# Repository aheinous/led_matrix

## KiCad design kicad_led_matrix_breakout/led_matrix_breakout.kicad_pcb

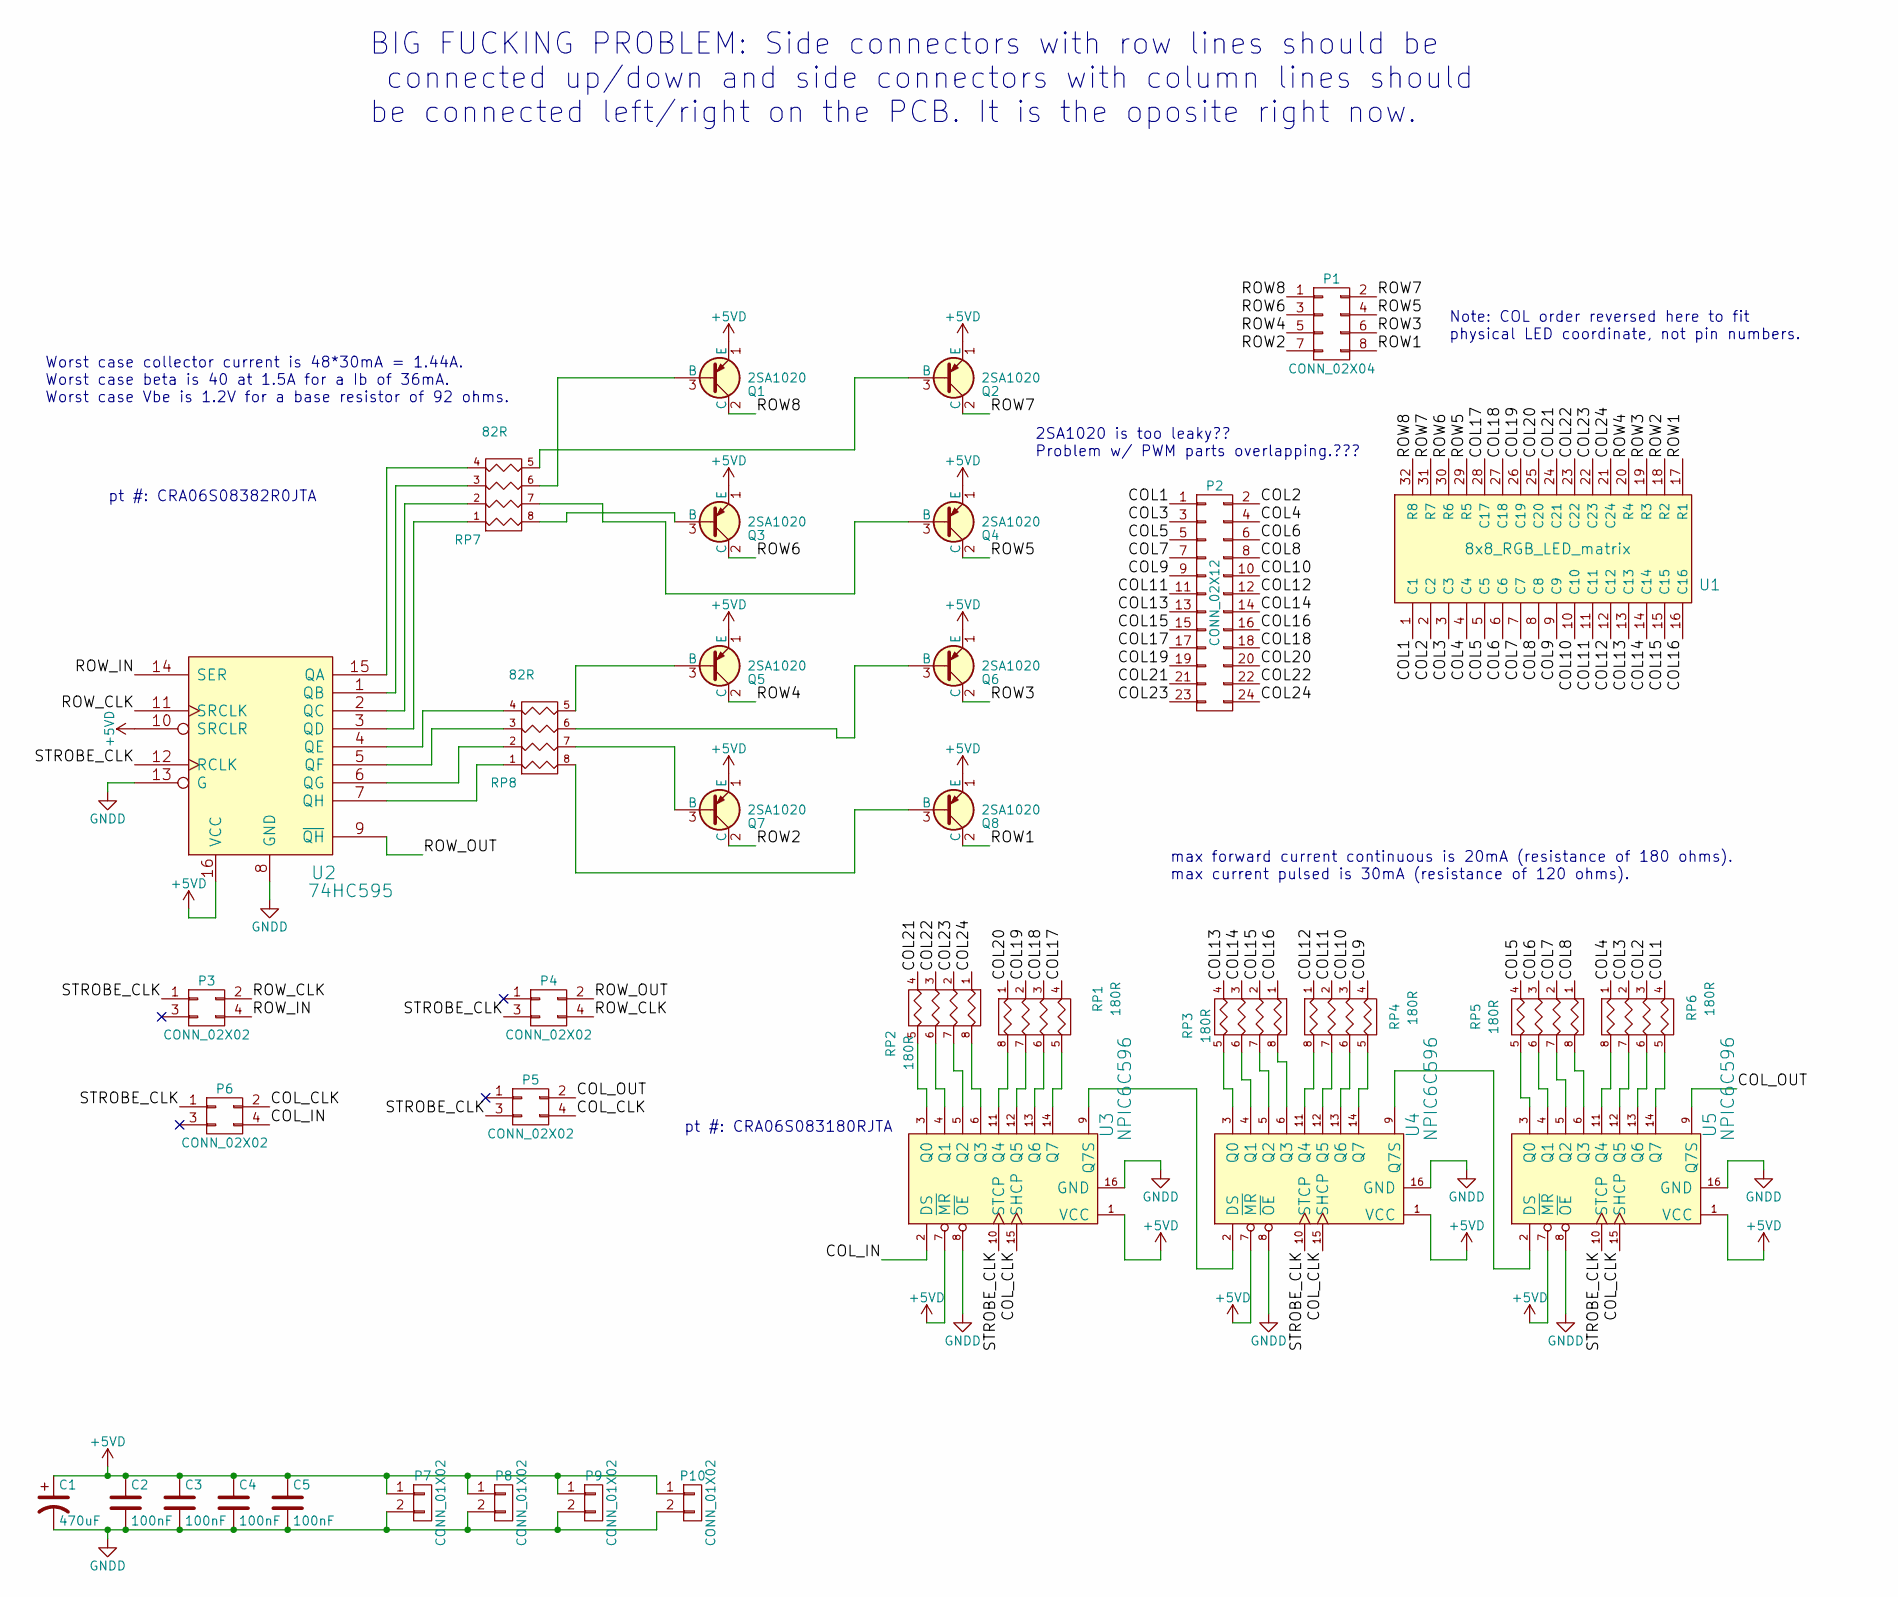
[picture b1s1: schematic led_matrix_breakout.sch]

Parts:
C1: 470uF; c_elec_10x10
C2, C3, C4, C5: 100nF; C_0805_HandSoldering
P1: CONN_02X04; Pin_Header_Straight_2x04
P2: CONN_02X12; Pin_Header_Straight_2x12
P3, P4, P5, P6: CONN_02X02; 2x2_edge_header_new
P7, P8, P9, P10: CONN_01X02; 2x1_edge_header_new
Q1, Q2, Q3, Q4, Q5, Q6, Q7, Q8: 2SA1020; TO-92_Inline_Narrow_Oval
RP1, RP2, RP3, RP4, RP5, RP6: 180R; CRA06S_4_resistor_array
RP7, RP8: 82R; CRA06S_4_resistor_array
U1: 8x8_RGB_LED_matrix; 8x8_RGB_led_matrix_60mmx60mm
U2: 74HC595; SSOP-16_4.4x5.2mm_Pitch0.65mm
U3, U4, U5: NPIC6C596; SSOP-16_4.4x5.2mm_Pitch0.65mm

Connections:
+5VD: C1.1, C2.1, C3.1, C4.1, C5.1, P7.1, P8.1, P9.1, P10.1, Q1.1 (E), Q2.1 (E), Q3.1 (E), Q4.1 (E), Q5.1 (E), Q6.1 (E), Q7.1 (E), Q8.1 (E), U2.10 (SRCLR), U2.16 (VCC), U3.1 (VCC), U3.7 (~MR), U4.1 (VCC), U4.7 (~MR), U5.1 (VCC), U5.7 (~MR)
/COL1: P2.1, RP6.4, U1.1 (C1); also elsewhere on the board
/COL2: P2.2, RP6.3, U1.2 (C2); also elsewhere on the board
/COL3: P2.3, RP6.2, U1.3 (C3); also elsewhere on the board
/COL4: P2.4, RP6.1, U1.4 (C4); also elsewhere on the board
/COL5: P2.5, RP5.4, U1.5 (C5); also elsewhere on the board
/COL6: P2.6, RP5.3, U1.6 (C6); also elsewhere on the board
/COL7: P2.7, RP5.2, U1.7 (C7); also elsewhere on the board
/COL8: P2.8, RP5.1, U1.8 (C8); also elsewhere on the board
/COL9: P2.9, RP4.4, U1.9 (C9); also elsewhere on the board
/COL10: P2.10, RP4.3, U1.10 (C10); also elsewhere on the board
/COL11: P2.11, RP4.2, U1.11 (C11); also elsewhere on the board
/COL12: P2.12, RP4.1, U1.12 (C12); also elsewhere on the board
/COL13: P2.13, RP3.4, U1.13 (C13); also elsewhere on the board
/COL14: P2.14, RP3.3, U1.14 (C14); also elsewhere on the board
/COL15: P2.15, RP3.2, U1.15 (C15); also elsewhere on the board
/COL16: P2.16, RP3.1, U1.16 (C16); also elsewhere on the board
/COL17: P2.17, RP1.4, U1.28 (C17); also elsewhere on the board
/COL18: P2.18, RP1.3, U1.27 (C18); also elsewhere on the board
/COL19: P2.19, RP1.2, U1.26 (C19); also elsewhere on the board
/COL20: P2.20, RP1.1, U1.25 (C20); also elsewhere on the board
/COL21: P2.21, RP2.4, U1.24 (C21); also elsewhere on the board
/COL22: P2.22, RP2.3, U1.23 (C22); also elsewhere on the board
/COL23: P2.23, RP2.2, U1.22 (C23); also elsewhere on the board
/COL24: P2.24, RP2.1, U1.21 (C24); also elsewhere on the board
/COL_CLK: P5.4, P6.2, U3.15 (SHCP), U4.15 (SHCP), U5.15 (SHCP)
/COL_IN: P6.4, U3.2 (DS)
/COL_OUT: P5.2, U5.9 (Q7S)
/ROW1: P1.8, Q8.2 (C), U1.17 (R1); also elsewhere on the board
/ROW2: P1.7, Q7.2 (C), U1.18 (R2); also elsewhere on the board
/ROW3: P1.6, Q6.2 (C), U1.19 (R3); also elsewhere on the board
/ROW4: P1.5, Q5.2 (C), U1.20 (R4); also elsewhere on the board
/ROW5: P1.4, Q4.2 (C), U1.29 (R5); also elsewhere on the board
/ROW6: P1.3, Q3.2 (C), U1.30 (R6); also elsewhere on the board
/ROW7: P1.2, Q2.2 (C), U1.31 (R7); also elsewhere on the board
/ROW8: P1.1, Q1.2 (C), U1.32 (R8); also elsewhere on the board
/ROW_CLK: P3.2, P4.4, U2.11 (SRCLK)
/ROW_IN: P3.4, U2.14 (SER)
/ROW_OUT: P4.2, U2.9 (~QH)
/STROBE_CLK: P3.1, P4.3, P5.3, P6.1, U2.12 (RCLK), U3.10 (STCP), U4.10 (STCP), U5.10 (STCP)
GNDD: C1.2, C2.2, C3.2, C4.2, C5.2, P7.2, P8.2, P9.2, P10.2, U2.8 (GND), U2.13 (G), U3.8 (~OE), U3.16 (GND), U4.8 (~OE), U4.16 (GND), U5.8 (~OE), U5.16 (GND)
unnamed: Q1.3 (B), RP7.6 (R3)
unnamed: Q2.3 (B), RP7.5 (R4)
unnamed: Q3.3 (B), RP7.8 (R1)
unnamed: Q4.3 (B), RP7.7 (R2)
unnamed: Q5.3 (B), RP8.5 (R4)
unnamed: Q6.3 (B), RP8.6 (R3)
unnamed: Q7.3 (B), RP8.7 (R2)
unnamed: Q8.3 (B), RP8.8 (R1)
unnamed: RP1.5 (R4), U3.14 (Q7)
unnamed: RP1.6 (R3), U3.13 (Q6)
unnamed: RP1.7 (R2), U3.12 (Q5)
unnamed: RP1.8 (R1), U3.11 (Q4)
unnamed: RP2.5 (R4), U3.3 (Q0)
unnamed: RP2.6 (R3), U3.4 (Q1)
unnamed: RP2.7 (R2), U3.5 (Q2)
unnamed: RP2.8 (R1), U3.6 (Q3)
unnamed: RP3.5 (R4), U4.3 (Q0)
unnamed: RP3.6 (R3), U4.4 (Q1)
unnamed: RP3.7 (R2), U4.5 (Q2)
unnamed: RP3.8 (R1), U4.6 (Q3)
unnamed: RP4.5 (R4), U4.14 (Q7)
unnamed: RP4.6 (R3), U4.13 (Q6)
unnamed: RP4.7 (R2), U4.12 (Q5)
unnamed: RP4.8 (R1), U4.11 (Q4)
unnamed: RP5.5 (R4), U5.3 (Q0)
unnamed: RP5.6 (R3), U5.4 (Q1)
unnamed: RP5.7 (R2), U5.5 (Q2)
unnamed: RP5.8 (R1), U5.6 (Q3)
unnamed: RP6.5 (R4), U5.14 (Q7)
unnamed: RP6.6 (R3), U5.13 (Q6)
unnamed: RP6.7 (R2), U5.12 (Q5)
unnamed: RP6.8 (R1), U5.11 (Q4)
unnamed: RP7.1, U2.3 (QD)
unnamed: RP7.2, U2.2 (QC)
unnamed: RP7.3, U2.1 (QB)
unnamed: RP7.4, U2.15 (QA)
unnamed: RP8.1, U2.7 (QH)
unnamed: RP8.2, U2.6 (QG)
unnamed: RP8.3, U2.5 (QF)
unnamed: RP8.4, U2.4 (QE)
unnamed: U3.9 (Q7S), U4.2 (DS)
unnamed: U4.9 (Q7S), U5.2 (DS)

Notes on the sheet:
max forward current continuous is 20mA (resistance of 180 ohms). max current pulsed is 30mA (resistance of 120 ohms).
Worst case collector current is 48*30mA = 1.44A. Worst case beta is 40 at 1.5A for a Ib of 36mA. Worst case Vbe is 1.2V for a base resistor of 92 ohms.
pt #: CRA06S08382R0JTA
pt #: CRA06S083180RJTA
Note: COL order reversed here to fit physical LED coordinate, not pin numbers.
BIG FUCKING PROBLEM: Side connectors with row lines should be connected up/down and side connectors with column lines should be connected left/right on the PCB. It is the oposite right now.
2SA1020 is too leaky?? Problem w/ PWM parts overlapping.???

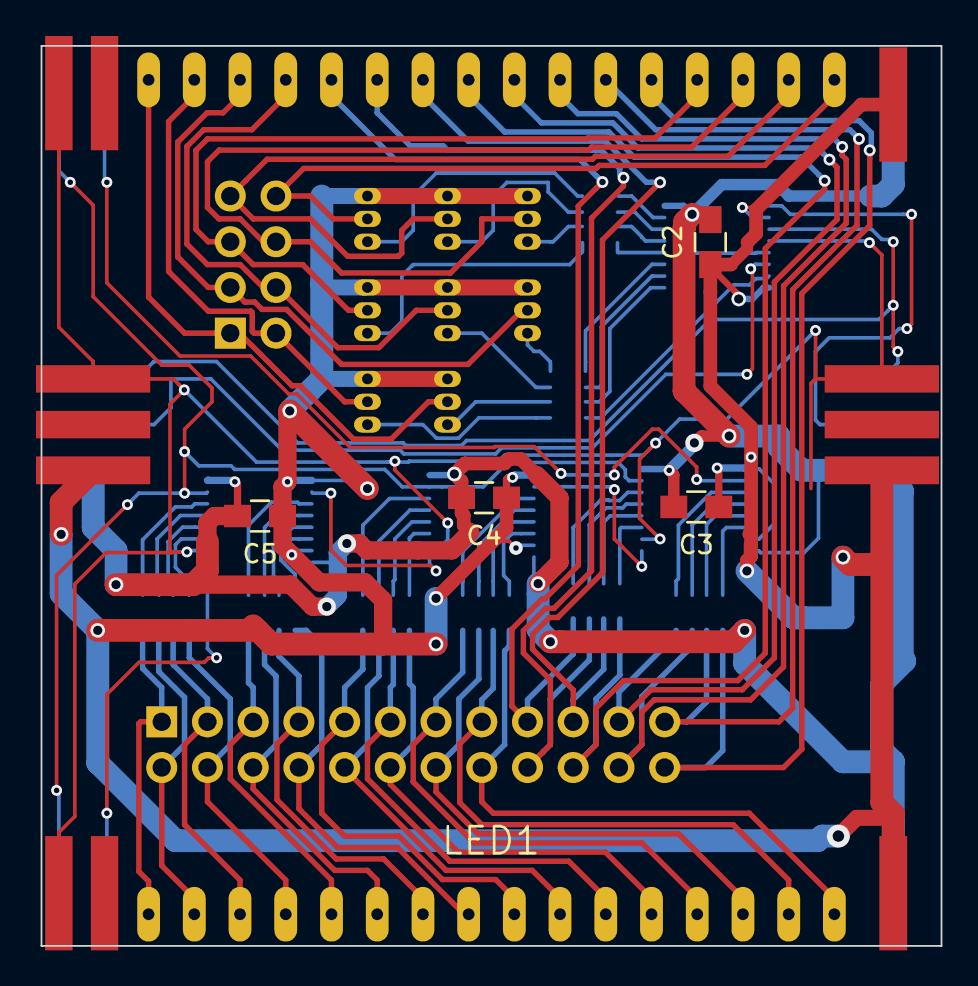
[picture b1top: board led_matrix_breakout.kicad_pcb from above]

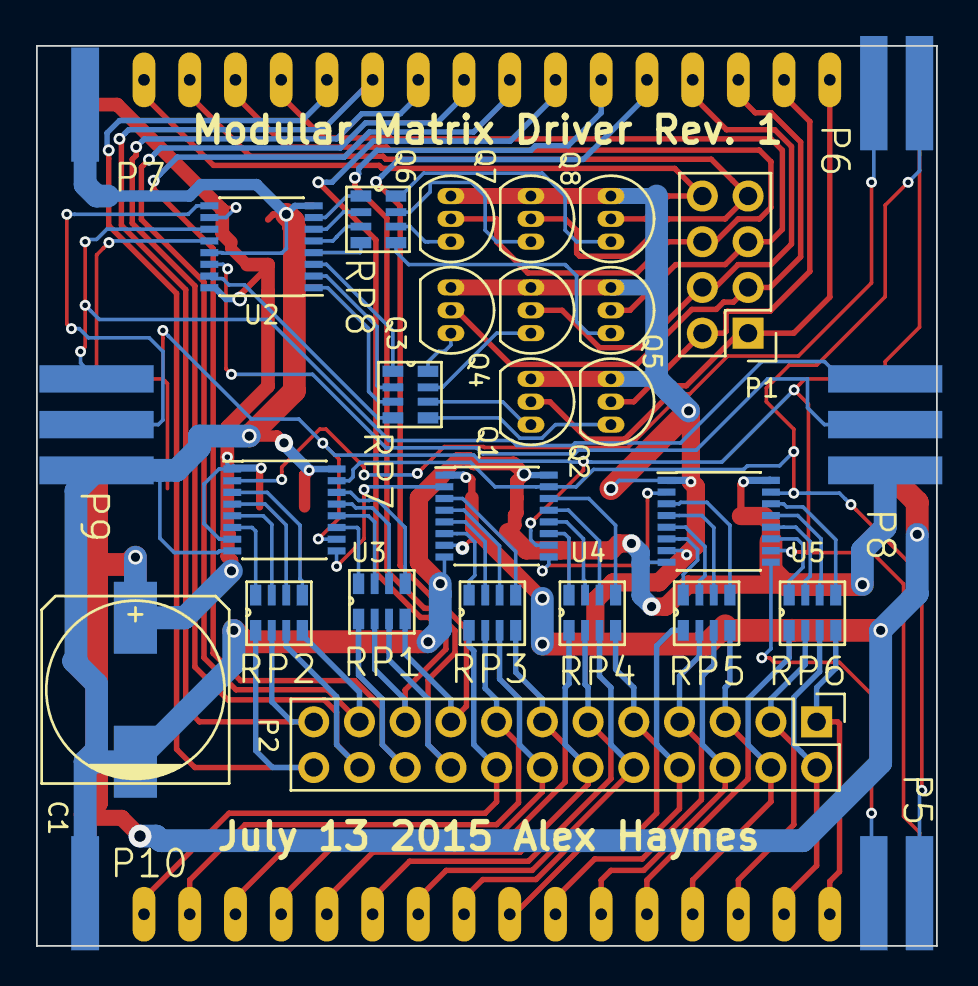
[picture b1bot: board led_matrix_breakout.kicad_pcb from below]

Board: 2 copper layers, 50.0 x 50.0 mm, 36 parts (31 on the bottom side), 83 nets.

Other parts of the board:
LED1: 8x8_RGB_LED_matrix; 8x8_RGB_led_matrix_60mmx60mm

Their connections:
/COL1: LED1.1; also elsewhere on the board
/COL2: LED1.2; also elsewhere on the board
/COL3: LED1.3; also elsewhere on the board
/COL4: LED1.4; also elsewhere on the board
/COL5: LED1.5; also elsewhere on the board
/COL6: LED1.6; also elsewhere on the board
/COL7: LED1.7; also elsewhere on the board
/COL8: LED1.8; also elsewhere on the board
/COL9: LED1.9; also elsewhere on the board
/COL10: LED1.10; also elsewhere on the board
/COL11: LED1.11; also elsewhere on the board
/COL12: LED1.12; also elsewhere on the board
/COL13: LED1.13; also elsewhere on the board
/COL14: LED1.14; also elsewhere on the board
/COL15: LED1.15; also elsewhere on the board
/COL16: LED1.16; also elsewhere on the board
/COL17: LED1.28; also elsewhere on the board
/COL18: LED1.27; also elsewhere on the board
/COL19: LED1.26; also elsewhere on the board
/COL20: LED1.25; also elsewhere on the board
/COL21: LED1.24; also elsewhere on the board
/COL22: LED1.23; also elsewhere on the board
/COL23: LED1.22; also elsewhere on the board
/COL24: LED1.21; also elsewhere on the board
/ROW1: LED1.17; also elsewhere on the board
/ROW2: LED1.18; also elsewhere on the board
/ROW3: LED1.19; also elsewhere on the board
/ROW4: LED1.20; also elsewhere on the board
/ROW5: LED1.29; also elsewhere on the board
/ROW6: LED1.30; also elsewhere on the board
/ROW7: LED1.31; also elsewhere on the board
/ROW8: LED1.32; also elsewhere on the board

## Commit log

2015-11-22 Added KiCad files.
2016-03-05 Changed led mapping to reflect physical layout quirk.
